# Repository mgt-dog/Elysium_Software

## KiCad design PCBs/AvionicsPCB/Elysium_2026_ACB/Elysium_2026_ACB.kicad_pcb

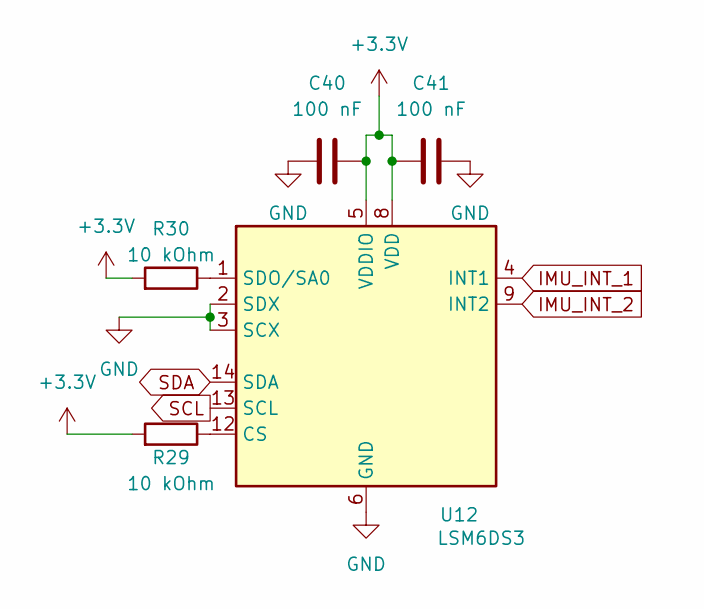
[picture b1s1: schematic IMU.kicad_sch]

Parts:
C40, C41: 100 nF; C_0603_1608Metric
R29, R30: 10 kOhm; R_0603_1608Metric
U12: LSM6DS3; LGA-14_3x2.5mm_P0.5mm_LayoutBorder3x4y

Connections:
+3.3V: C40.2, C41.1, R29.2, R30.2, U12.5 (VDDIO), U12.8 (VDD); also elsewhere on the board
GND: C40.1, C41.2, U12.2 (SDX), U12.3 (SCX), U12.6 (GND), U12.7 (GND); also elsewhere on the board
IMU_INT_1: U12.4 (INT1); also elsewhere on the board
IMU_INT_2: U12.9 (INT2); also elsewhere on the board
unnamed: R29.1, U12.12 (CS)
unnamed: R30.1, U12.1 (SDO/SA0)
SCL: U12.13 (SCL); also elsewhere on the board
SDA: U12.14 (SDA); also elsewhere on the board

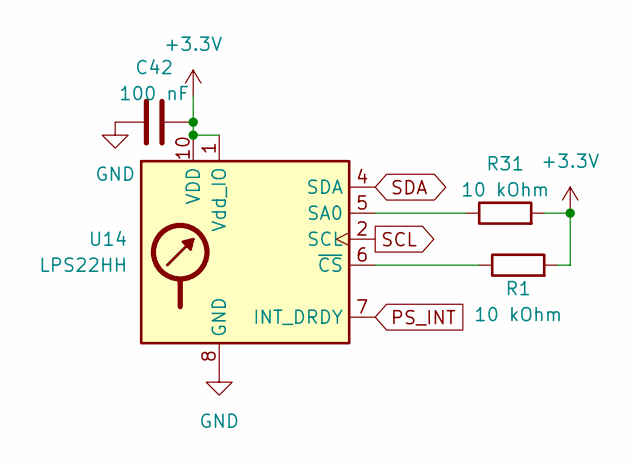
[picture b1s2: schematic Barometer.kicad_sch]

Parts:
C42: 100 nF; C_0603_1608Metric
R1, R31: 10 kOhm; R_0603_1608Metric
U14: LPS22HH; ST_HLGA-10_2x2mm_P0.5mm_LayoutBorder3x2y

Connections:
+3.3V: C42.2, R1.2, R31.2, U14.1 (Vdd_IO), U14.10 (VDD); also elsewhere on the board
GND: C42.1, U14.3 (GND), U14.8 (GND), U14.9 (GND); also elsewhere on the board
unnamed: R31.1, U14.5 (SA0)
unnamed: R1.1, U14.6 (~CS)
PS_INT: U14.7 (INT_DRDY); also elsewhere on the board
SCL: U14.2 (SCL); also elsewhere on the board
SDA: U14.4 (SDA); also elsewhere on the board

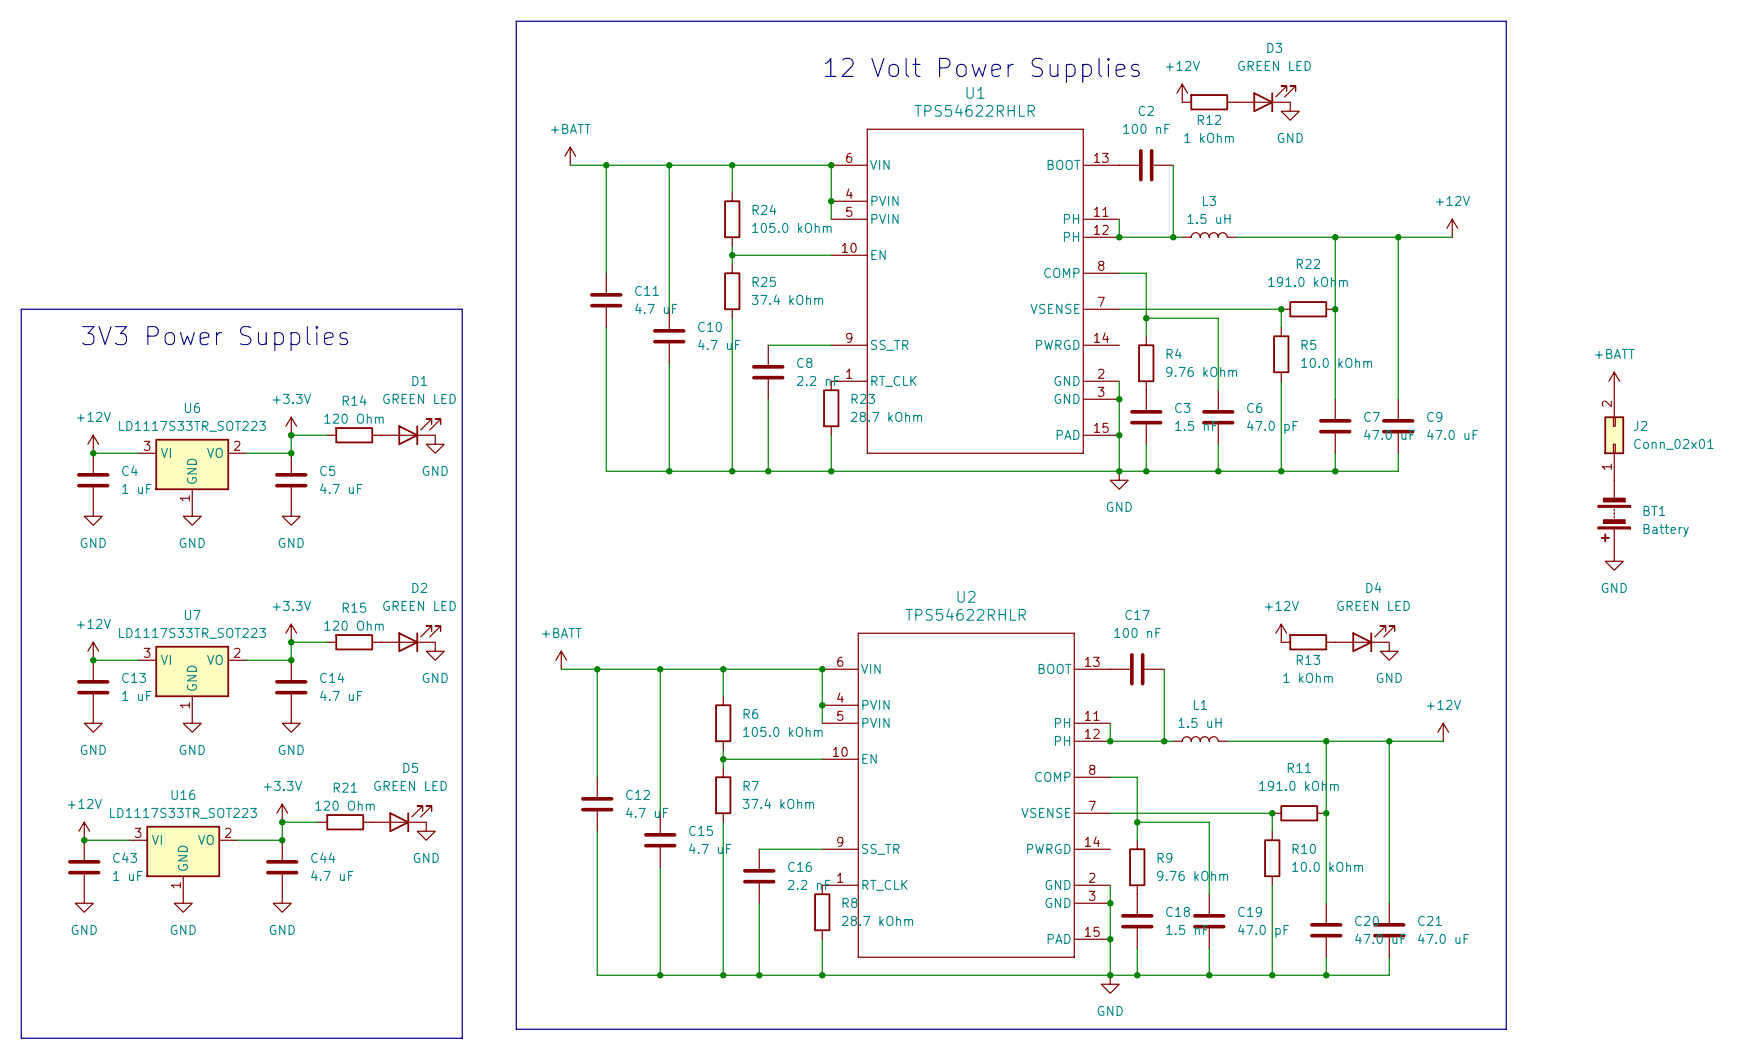
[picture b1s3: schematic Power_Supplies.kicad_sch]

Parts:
BT1: Battery; TerminalBlock_WAGO_2601-3102_1x02_P3.50mm_Vertical
C2, C17: 100 nF; C_0805_2012Metric
C3, C18: 1.5 nF; C_0805_2012Metric
C4, C13, C43: 1 uF; C_0603_1608Metric
C5, C14, C44: 4.7 uF; C_0603_1608Metric
C6, C19: 47.0 pF; C_0805_2012Metric
C7, C9, C20, C21: 47.0 uF; C_1210_3225Metric
C8, C16: 2.2 nF; C_0805_2012Metric
C10, C15: 4.7 uF; C_0805_2012Metric
C11, C12: 4.7 uF; C_1206_3216Metric
D1, D2, D3, D4, D5: GREEN LED; LED_0805_2012Metric
J2: Conn_02x01; TerminalBlock_WAGO_2601-3102_1x02_P3.50mm_Vertical
L1, L3: 1.5 uH; WE-XHMI_4030
R4, R9: 9.76 kOhm; R_0805_2012Metric
R5, R10: 10.0 kOhm; R_0805_2012Metric
R6, R24: 105.0 kOhm; R_0805_2012Metric
R7, R25: 37.4 kOhm; R_0805_2012Metric
R8, R23: 28.7 kOhm; R_0805_2012Metric
R11, R22: 191.0 kOhm; R_0805_2012Metric
R12, R13: 1 kOhm; R_0603_1608Metric
R14, R15, R21: 120 Ohm; R_0603_1608Metric
U1, U2: TPS54622RHLR; RHL0014A
U6, U7, U16: LD1117S33TR_SOT223; SOT-223-3_TabPin2

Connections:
+3.3V: C5.1, C14.1, C44.1, R14.2, R15.2, R21.2, U6.2 (VO), U7.2 (VO), U16.2 (VO); also elsewhere on the board
+12V: C4.1, C7.2, C9.2, C13.1, C20.2, C21.2, C43.1, L1.2, L3.2, R11.2, R12.2, R13.2, R22.2, U6.3 (VI), U7.3 (VI), U16.3 (VI); also elsewhere on the board
+BATT: C10.2, C11.2, C12.2, C15.2, J2.2, R6.1, R24.1, U1.4 (PVIN), U1.5 (PVIN), U1.6 (VIN), U2.4 (PVIN), U2.5 (PVIN), U2.6 (VIN)
GND: BT1.1 (+), C3.1, C4.2, C5.2, C6.1, C7.1, C8.1, C9.1, C10.1, C11.1, C12.1, C13.2, C14.2, C15.1, C16.1, C18.1, C19.1, C20.1, C21.1, C43.2, C44.2, D1.1 (K), D2.1 (K), D3.1 (K), D4.1 (K), D5.1 (K), R5.2, R7.2, R8.2, R10.2, R23.2, R25.2, U1.2 (GND), U1.3 (GND), U1.15 (PAD), U2.2 (GND), U2.3 (GND), U2.15 (PAD), U6.1 (GND), U7.1 (GND), U16.1 (GND); also elsewhere on the board
unnamed: BT1.2 (-), J2.1
unnamed: C2.1, L3.1, U1.11 (PH), U1.12 (PH)
unnamed: C3.2, R4.2
unnamed: C17.1, L1.1, U2.11 (PH), U2.12 (PH)
unnamed: C18.2, R9.2
unnamed: D1.2 (A), R14.1
unnamed: D2.2 (A), R15.1
unnamed: D3.2 (A), R12.1
unnamed: D4.2 (A), R13.1
unnamed: D5.2 (A), R21.1
unnamed: C2.2, U1.13 (BOOT)
unnamed: C6.2, R4.1, U1.8 (COMP)
unnamed: R24.2, R25.1, U1.10 (EN)
unnamed: R23.1, U1.1 (RT_CLK)
unnamed: C8.2, U1.9 (SS_TR)
unnamed: R5.1, R22.1, U1.7 (VSENSE)
unnamed: C17.2, U2.13 (BOOT)
unnamed: C19.2, R9.1, U2.8 (COMP)
unnamed: R6.2, R7.1, U2.10 (EN)
unnamed: R8.1, U2.1 (RT_CLK)
unnamed: C16.2, U2.9 (SS_TR)
unnamed: R10.1, R11.1, U2.7 (VSENSE)

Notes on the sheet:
3V3 Power Supplies
12 Volt Power Supplies

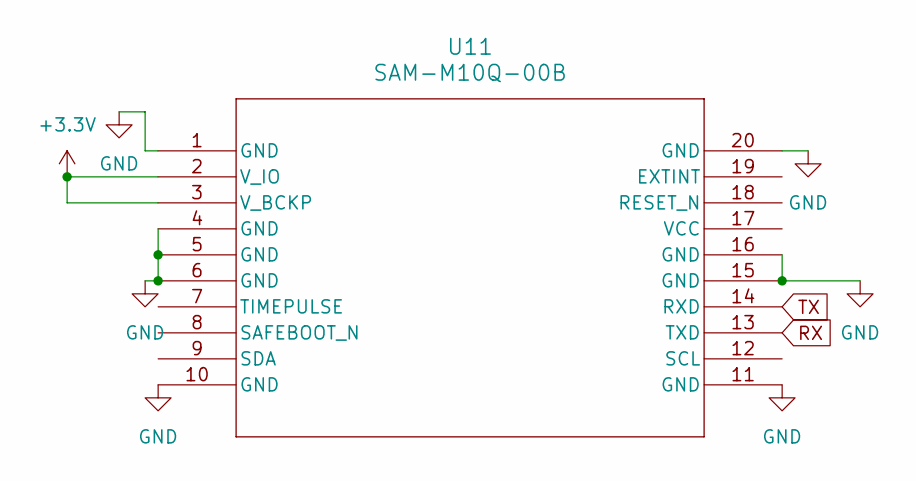
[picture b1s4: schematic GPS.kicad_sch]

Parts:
U11: SAM-M10Q-00B; SAM-M10Q_UBL

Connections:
+3.3V: U11.2 (V_IO), U11.3 (V_BCKP); also elsewhere on the board
GND: U11.1 (GND), U11.4 (GND), U11.5 (GND), U11.6 (GND), U11.10 (GND), U11.11 (GND), U11.15 (GND), U11.16 (GND), U11.20 (GND); also elsewhere on the board
RX: U11.13 (TXD); also elsewhere on the board
TX: U11.14 (RXD); also elsewhere on the board

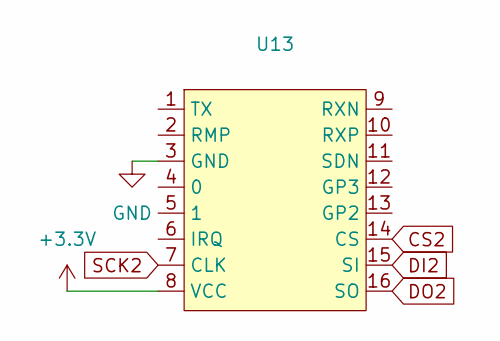
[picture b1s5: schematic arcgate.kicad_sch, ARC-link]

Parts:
U13: HC-12 ARC-link

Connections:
+3.3V: U13.8 (VCC); also elsewhere on the board
CS2: U13.14 (CS); also elsewhere on the board
DI2: U13.15 (SI); also elsewhere on the board
DO2: U13.16 (SO); also elsewhere on the board
GND: U13.3 (GND); also elsewhere on the board
SCK2: U13.7 (CLK); also elsewhere on the board

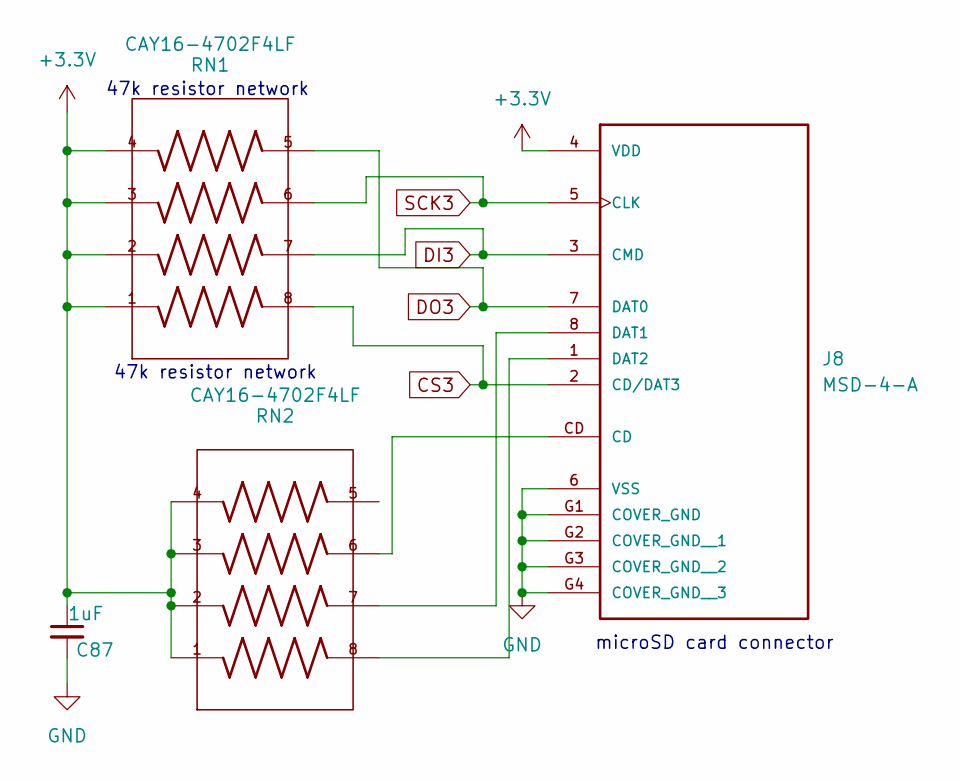
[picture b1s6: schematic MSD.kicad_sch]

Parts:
C87: 1uF; C_0603_1608Metric
J8: MSD-4-A; CUI_MSD-4-A
RN1, RN2: CAY16-4702F4LF; R_Array_Convex_4x1206

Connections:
+3.3V: C87.1, J8.4 (VDD), RN1.1, RN1.2, RN1.3, RN1.4, RN2.1, RN2.2, RN2.3, RN2.4; also elsewhere on the board
CS3: J8.2 (CD/DAT3), RN1.8; also elsewhere on the board
DI3: J8.3 (CMD), RN1.7; also elsewhere on the board
DO3: J8.7 (DAT0), RN1.5; also elsewhere on the board
GND: C87.2, J8.6 (VSS), J8.G1 (COVER_GND), J8.G2 (COVER_GND__1), J8.G3 (COVER_GND__2), J8.G4 (COVER_GND__3); also elsewhere on the board
unnamed: J8.8 (DAT1), RN2.7
unnamed: J8.1 (DAT2), RN2.8
unnamed: J8.CD, RN2.6
SCK3: J8.5 (CLK), RN1.6; also elsewhere on the board

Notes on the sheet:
47k resistor network
microSD card connector

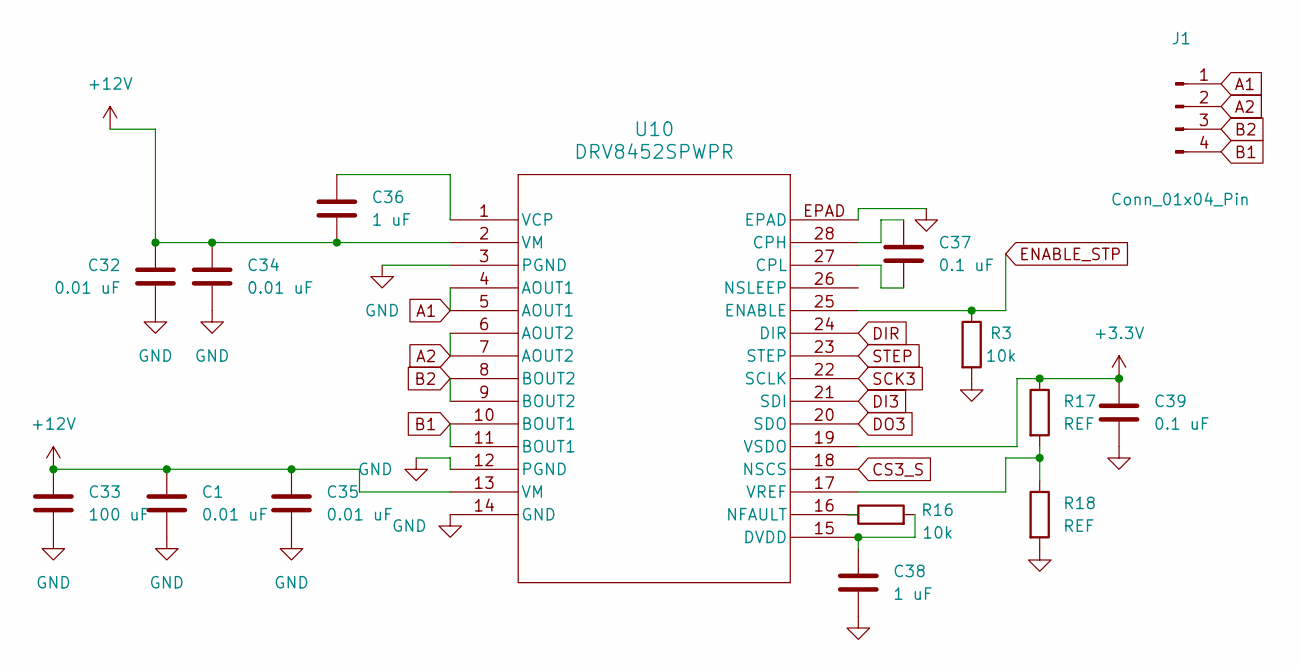
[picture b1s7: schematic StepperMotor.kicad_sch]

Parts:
C1, C32, C34, C35: 0.01 uF; C_0603_1608Metric
C33: 100 uF; CP_Radial_D10.0mm_P5.00mm
C36, C38: 1 uF; C_0603_1608Metric
C37, C39: 0.1 uF; C_0603_1608Metric
J1: Conn_01x04_Pin; CONN_B04B-PASK_JST
R3, R16: 10k; R_0603_1608Metric
R17, R18: REF; R_0603_1608Metric
U10: DRV8452SPWPR; PWP0028M_TEX

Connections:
+3.3V: C39.1, R17.1, U10.19 (VSDO); also elsewhere on the board
+12V: C1.1, C32.1, C33.1, C34.1, C35.1, C36.2, U10.2 (VM), U10.13 (VM); also elsewhere on the board
A1: J1.1, U10.4 (AOUT1), U10.5 (AOUT1)
A2: J1.2, U10.6 (AOUT2), U10.7 (AOUT2)
B1: J1.4, U10.10 (BOUT1), U10.11 (BOUT1)
B2: J1.3, U10.8 (BOUT2), U10.9 (BOUT2)
CS3_S: U10.18 (NSCS); also elsewhere on the board
DI3: U10.21 (SDI); also elsewhere on the board
DIR: U10.24 (DIR); also elsewhere on the board
DO3: U10.20 (SDO); also elsewhere on the board
ENABLE_STP: R3.1, U10.25 (ENABLE); also elsewhere on the board
GND: C1.2, C32.2, C33.2, C34.2, C35.2, C38.2, C39.2, R3.2, R18.2, U10.3 (PGND), U10.12 (PGND), U10.14 (GND), U10.EPAD; also elsewhere on the board
unnamed: C37.1, U10.28 (CPH)
unnamed: C37.2, U10.27 (CPL)
unnamed: C38.1, R16.2, U10.15 (DVDD)
unnamed: R16.1, U10.16 (NFAULT)
unnamed: C36.1, U10.1 (VCP)
unnamed: R17.2, R18.1, U10.17 (VREF)
SCK3: U10.22 (SCLK); also elsewhere on the board
STEP: U10.23 (STEP); also elsewhere on the board

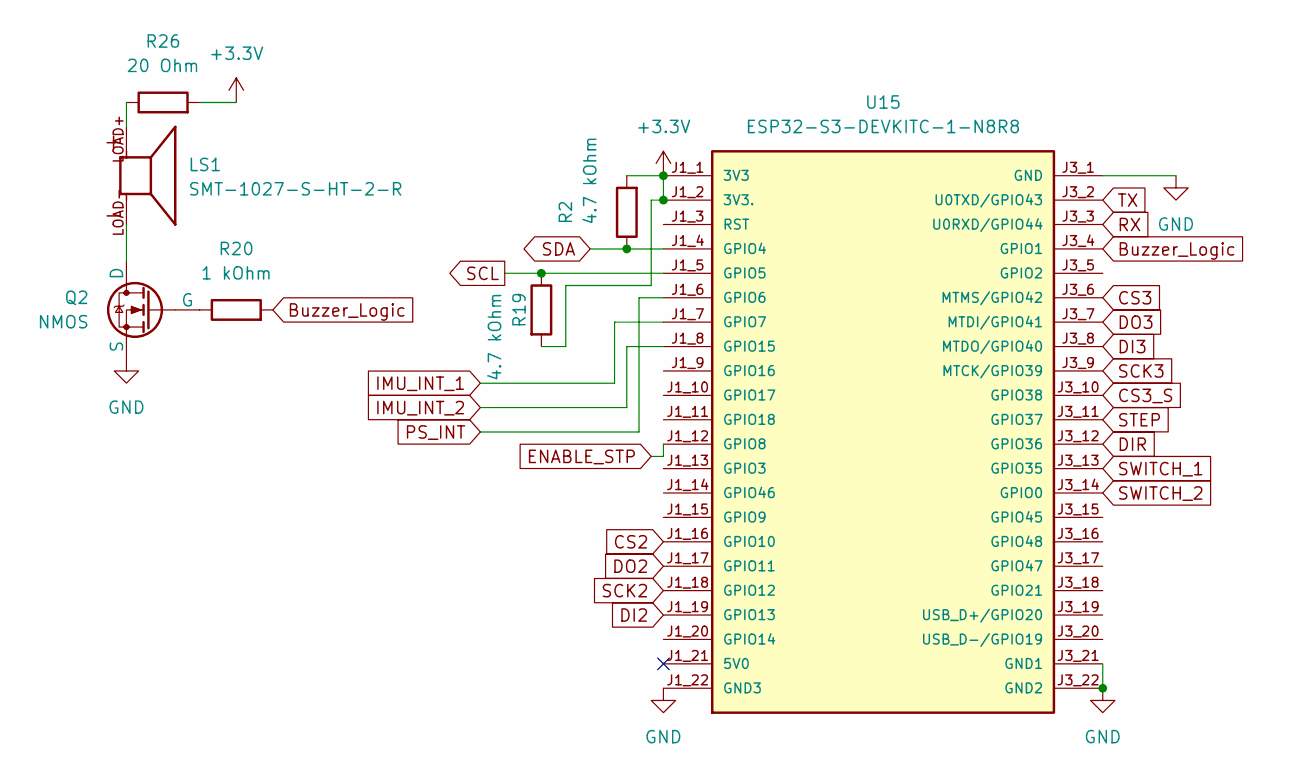
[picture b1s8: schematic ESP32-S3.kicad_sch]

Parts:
LS1: SMT-1027-S-HT-2-R; XDCR_SMT-1027-S-HT-2-R; PARTREV 3/26/20; DigiKey_Part_Number 668-SMT-1027-S-HT-2-RCT-ND
Q2: NMOS; SOT-23_GSFC0201_GAS
R2, R19: 4.7 kOhm; R_0603_1608Metric
R20: 1 kOhm; C_0603_1608Metric
R26: 20 Ohm; R_2512_6332Metric
U15: ESP32-S3-DEVKITC-1-N8R8

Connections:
+3.3V: R2.2, R19.2, R26.2, U15.J1_1 (3V3), U15.J1_2 (3V3.); also elsewhere on the board
Buzzer_Logic: R20.2, U15.J3_4 (GPIO1)
CS2: U15.J1_16 (GPIO10); also elsewhere on the board
CS3: U15.J3_6 (MTMS/GPIO42); also elsewhere on the board
CS3_S: U15.J3_10 (GPIO38); also elsewhere on the board
DI2: U15.J1_19 (GPIO13); also elsewhere on the board
DI3: U15.J3_8 (MTDO/GPIO40); also elsewhere on the board
DIR: U15.J3_12 (GPIO36); also elsewhere on the board
DO2: U15.J1_17 (GPIO11); also elsewhere on the board
DO3: U15.J3_7 (MTDI/GPIO41); also elsewhere on the board
ENABLE_STP: U15.J1_12 (GPIO8); also elsewhere on the board
GND: Q2.3 (S), U15.J1_22 (GND3), U15.J3_1 (GND), U15.J3_21 (GND1), U15.J3_22 (GND2); also elsewhere on the board
IMU_INT_1: U15.J1_7 (GPIO7); also elsewhere on the board
IMU_INT_2: U15.J1_8 (GPIO15); also elsewhere on the board
unnamed: LS1.LOAD+, R26.1
unnamed: LS1.LOAD-, Q2.1 (D)
unnamed: Q2.2 (G), R20.1
PS_INT: U15.J1_6 (GPIO6); also elsewhere on the board
RX: U15.J3_3 (U0RXD/GPIO44); also elsewhere on the board
SCK2: U15.J1_18 (GPIO12); also elsewhere on the board
SCK3: U15.J3_9 (MTCK/GPIO39); also elsewhere on the board
SCL: R19.1, U15.J1_5 (GPIO5); also elsewhere on the board
SDA: R2.1, U15.J1_4 (GPIO4); also elsewhere on the board
STEP: U15.J3_11 (GPIO37); also elsewhere on the board
SWITCH_1: U15.J3_13 (GPIO35); also elsewhere on the board
SWITCH_2: U15.J3_14 (GPIO0); also elsewhere on the board
TX: U15.J3_2 (U0TXD/GPIO43); also elsewhere on the board

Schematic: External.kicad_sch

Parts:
J3, J4: B02B-PASK-1; CONN_B02B-PASK-1_JST
R27, R28: 3.3 kOhm; C_0603_1608Metric

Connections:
GND: J3.2, J4.2; also elsewhere on the board
unnamed: J3.1, R28.2
unnamed: J4.1, R27.2
SWITCH_1: R27.1; also elsewhere on the board
SWITCH_2: R28.1; also elsewhere on the board

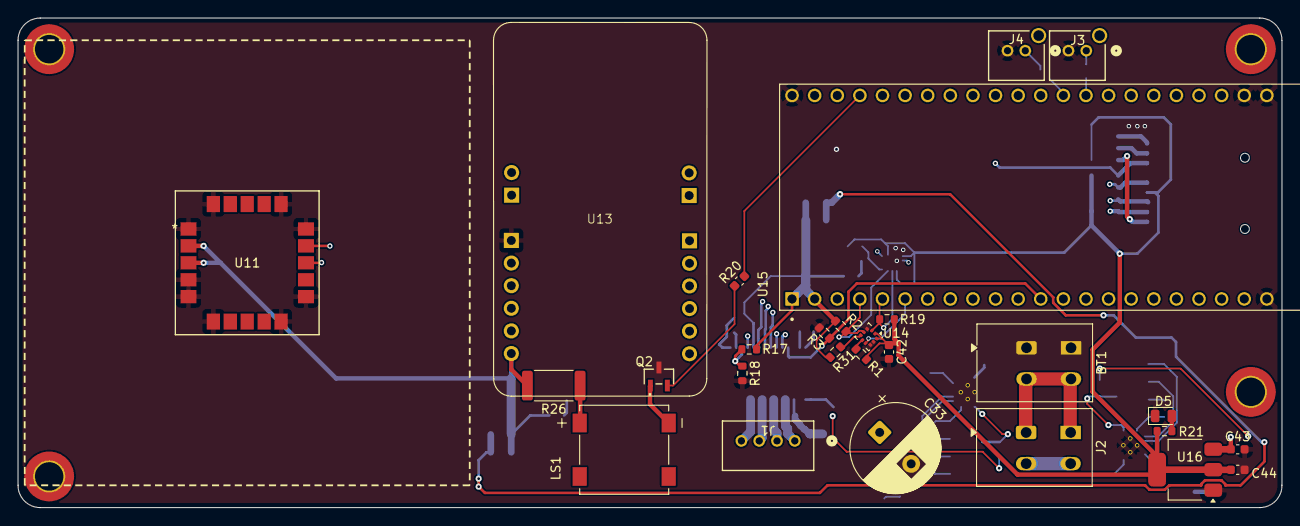
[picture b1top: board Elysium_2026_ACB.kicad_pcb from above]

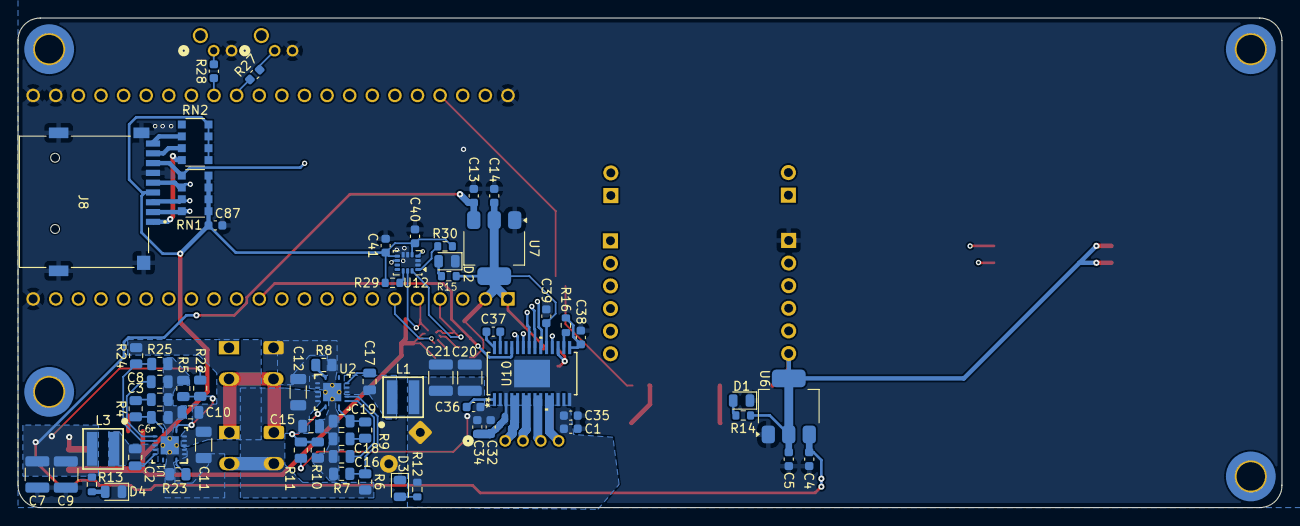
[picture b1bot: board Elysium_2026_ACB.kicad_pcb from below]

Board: 4 copper layers, 142.0 x 55.0 mm, 94 parts (67 on the bottom side), 70 nets.

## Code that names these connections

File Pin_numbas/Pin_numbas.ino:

#define SDA 4 
#define SCL 5
#define TX 43
#define RX 44
#define SCK3 39
#define D03 41
#define DI3 40
#define CS3 42
#define CS3_S 38
#define STEP 37
#define DIR 36
#define CS2 16
#define D02 17
#define SCK2 18
#define DI2 19

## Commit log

2026-01-12 initial test commit
2026-01-16 adding new directory
2026-01-16 my second commit
2026-01-22 Create Testing2
2026-01-22 nicklaus first commit pussies
2026-01-22 Adding Avionics Code
2026-01-22 payload pcb addition
2026-01-22 adding initial GPS
2026-01-22 Started calc altitude
2026-01-23 Apogee calculation updates
2026-01-26 adding GPS stuff
2026-01-26 adding LPS data
2026-01-26 adding LSM
2026-01-29 Create Pin_numbas.ino
    pin numbas
2026-01-29 pin numbas
    pin numbas
2026-01-29 maddy
2026-01-29 maddy again
2026-01-29 Changed to LPS25
2026-01-29 Untested RK4 code
    I think that I finished the general RK4 stuff somewhat. Gonna test for accuracy later this week once I get the time. If inaccurate there are some changes I can make like adding trapezoidal integratio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
2026-01-29 maddy git check
2026-01-29 alkdjfalkjd
2026-01-29 testing github bot
2026-01-29 added state machine basics
2026-01-29 missed a parenthesis
2026-01-29 Updated calcvelocity
2026-01-29 fixing acceleration for descent
2026-01-30 fixing a merge issue
